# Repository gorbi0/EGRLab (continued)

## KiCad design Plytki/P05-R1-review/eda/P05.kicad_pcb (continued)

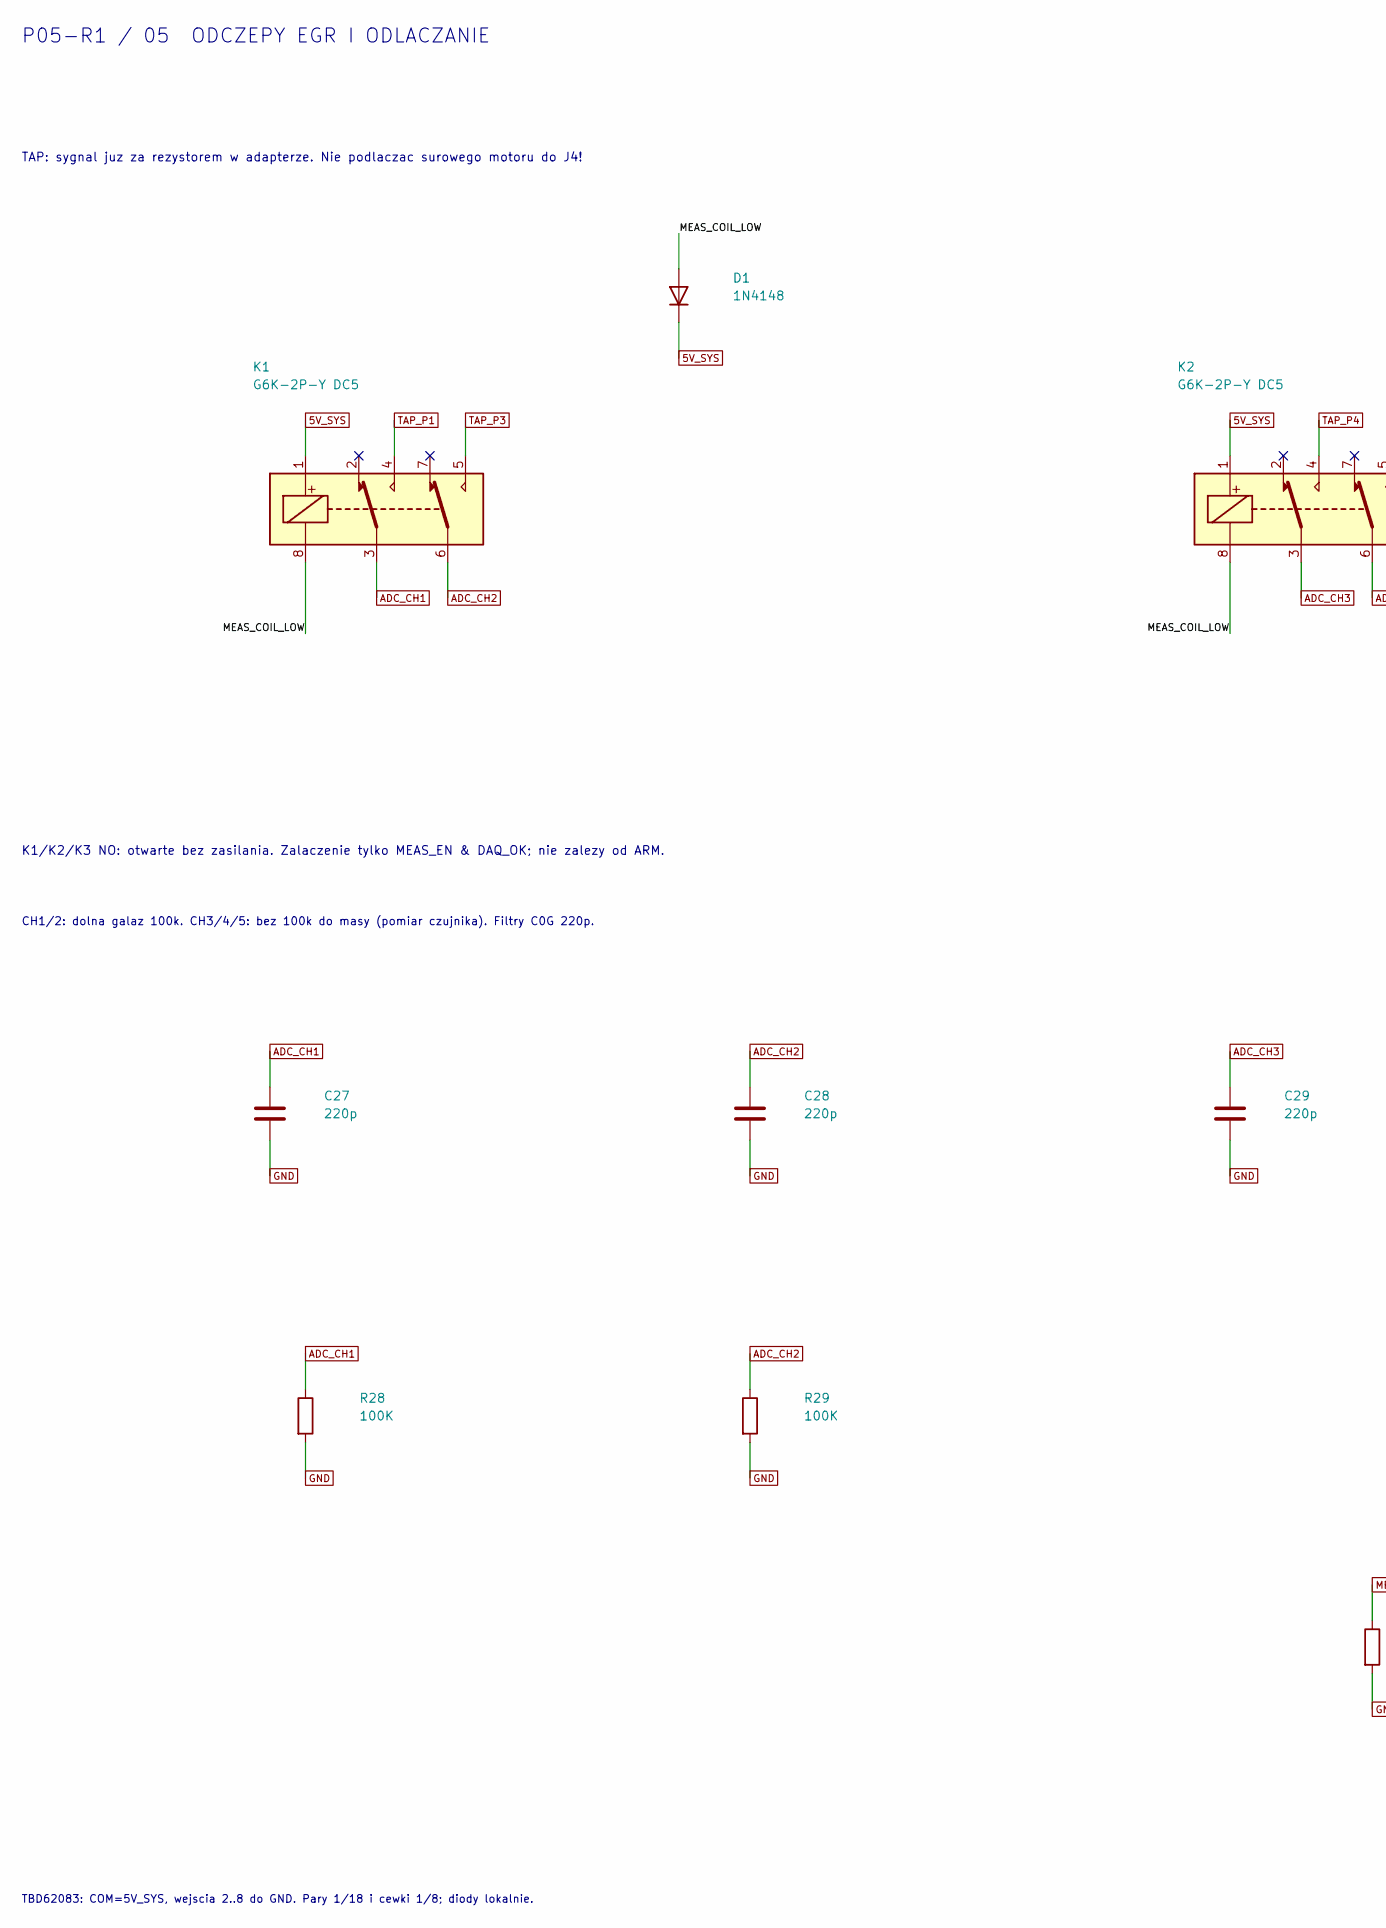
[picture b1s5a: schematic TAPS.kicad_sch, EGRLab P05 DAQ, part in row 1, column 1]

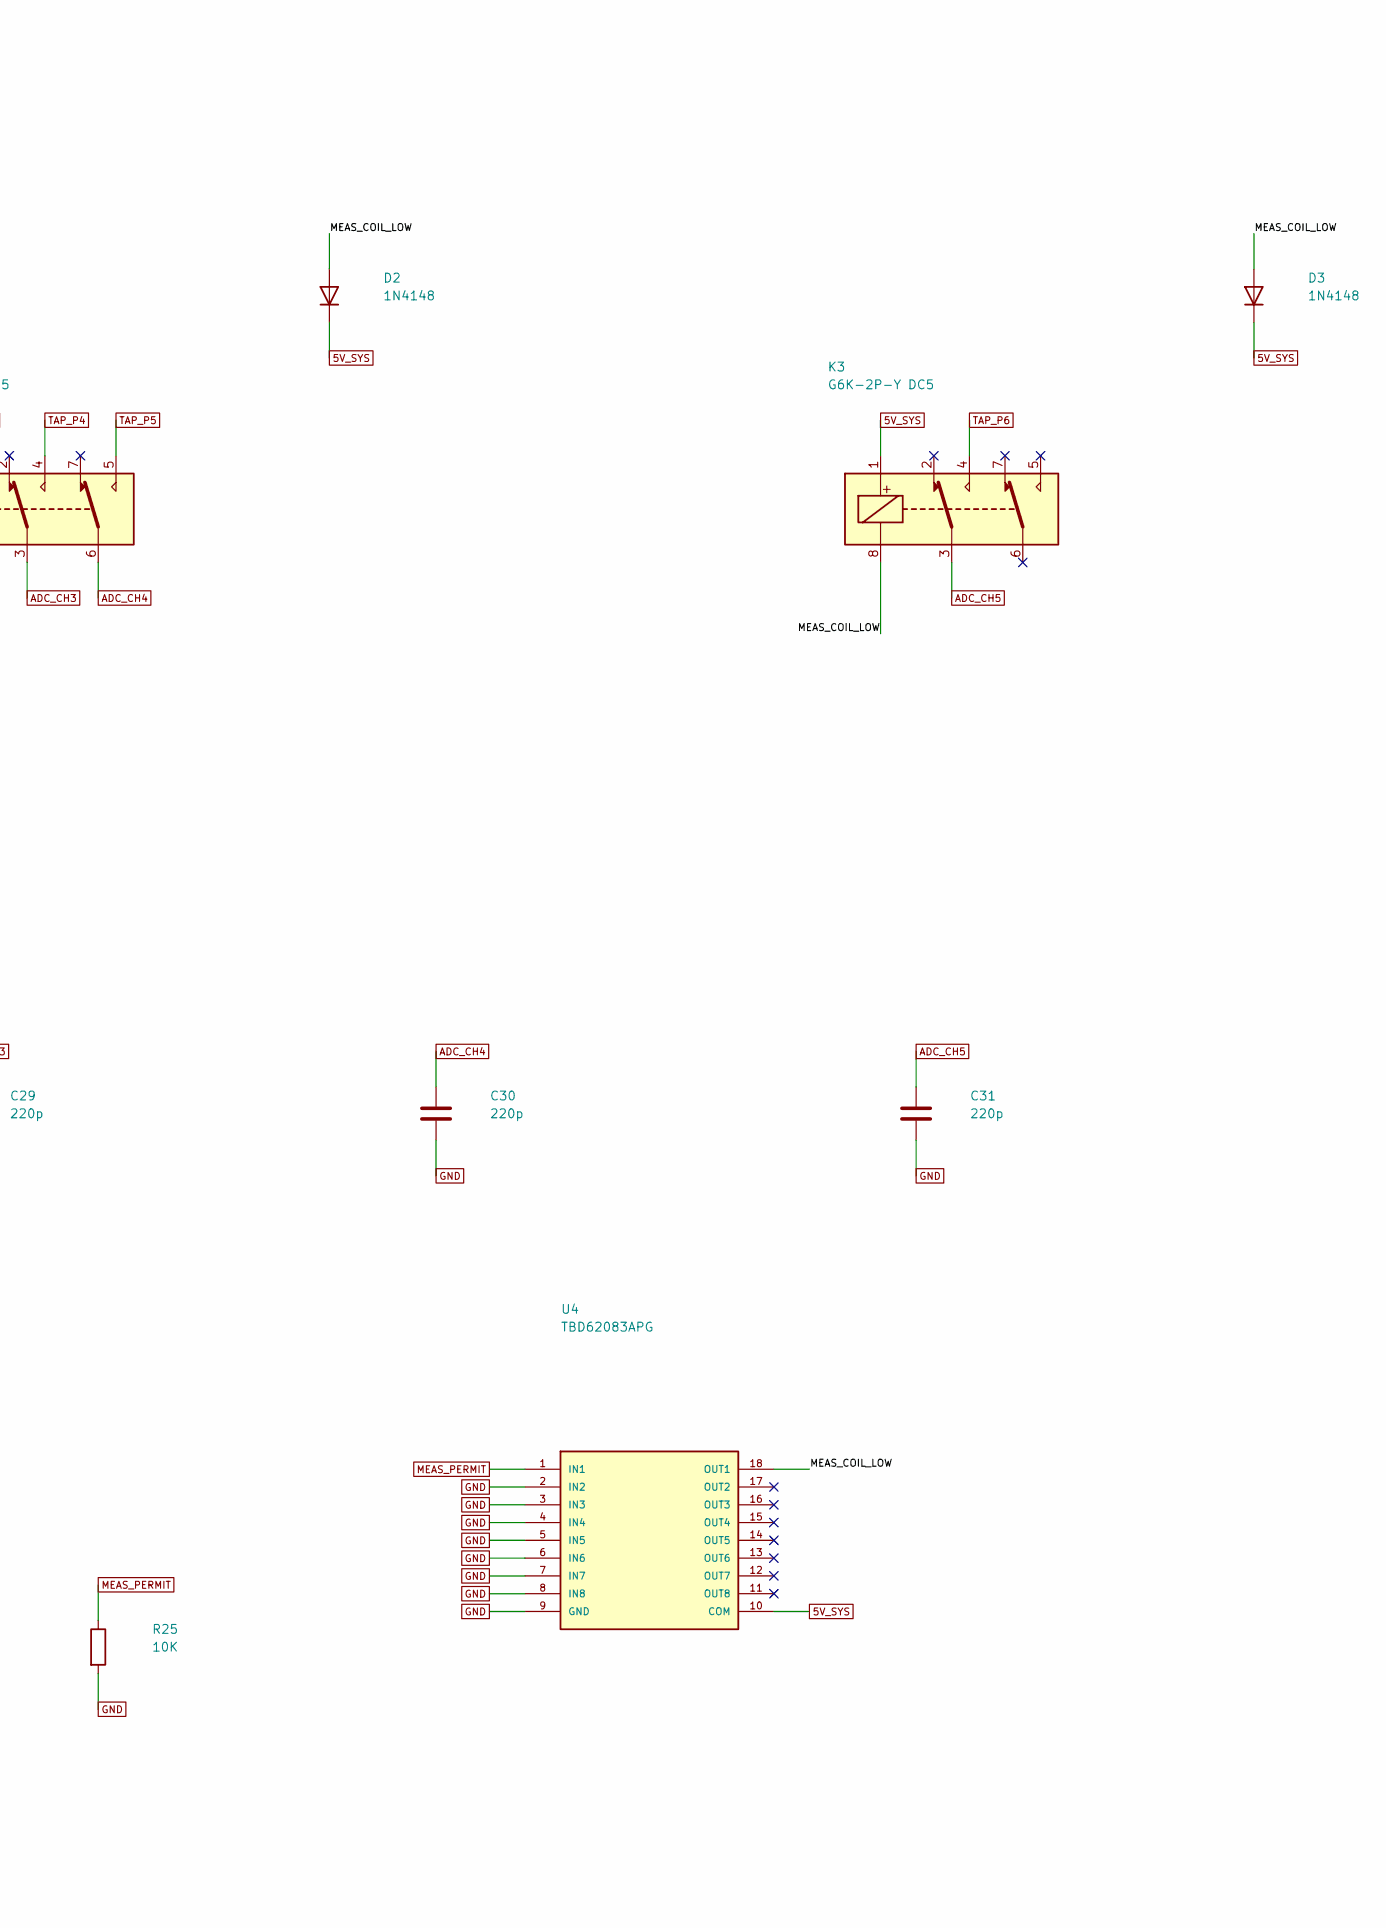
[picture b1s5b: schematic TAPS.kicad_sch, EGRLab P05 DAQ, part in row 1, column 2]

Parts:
C27, C28, C29, C30, C31: 220p; C_0805_2012Metric; MPN C0G 50V 5% 220p
D1, D2, D3: 1N4148; D_DO-35_SOD27_P7.62mm_Horizontal; MPN 1N4148
K1, K2, K3: G6K-2P-Y DC5; Relay_DPDT_Omron_G6K-2P-Y; MPN G6K-2P-Y DC5
R25: 10K; R_Axial_DIN0207_L6.3mm_D2.5mm_P10.16mm_Horizontal; MPN metal film resistor 10K 1%
R28, R29: 100K; R_Axial_DIN0207_L6.3mm_D2.5mm_P10.16mm_Horizontal; MPN MBB0207 precision metal film 100K 0.1%
U4: TBD62083APG; DIP-18_W7.62mm; MPN TBD62083APG

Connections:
5V_SYS: D1.1 (K), D2.1 (K), D3.1 (K), K1.1, K2.1, K3.1, U4.10 (COM); also elsewhere on the board
/TAPS/MEAS_COIL_LOW: D1.2 (A), D2.2 (A), D3.2 (A), K1.8, K2.8, K3.8, U4.18 (OUT1)
ADC_CH1: C27.1, K1.3, R28.1; also elsewhere on the board
ADC_CH2: C28.1, K1.6, R29.1; also elsewhere on the board
ADC_CH3: C29.1, K2.3; also elsewhere on the board
ADC_CH4: C30.1, K2.6; also elsewhere on the board
ADC_CH5: C31.1, K3.3; also elsewhere on the board
GND: C27.2, C28.2, C29.2, C30.2, C31.2, R25.2, R28.2, R29.2, U4.2 (IN2), U4.3 (IN3), U4.4 (IN4), U4.5 (IN5), U4.6 (IN6), U4.7 (IN7), U4.8 (IN8), U4.9 (GND); also elsewhere on the board
MEAS_PERMIT: R25.1, U4.1 (IN1); also elsewhere on the board
TAP_P1: K1.4; also elsewhere on the board
TAP_P3: K1.5; also elsewhere on the board
TAP_P4: K2.4; also elsewhere on the board
TAP_P5: K2.5; also elsewhere on the board
TAP_P6: K3.4; also elsewhere on the board

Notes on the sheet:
TAP: sygnal juz za rezystorem w adapterze. Nie podlaczac surowego motoru do J4!
K1/K2/K3 NO: otwarte bez zasilania. Zalaczenie tylko MEAS_EN & DAQ_OK; nie zalezy od ARM.
CH1/2: dolna galaz 100k. CH3/4/5: bez 100k do masy (pomiar czujnika). Filtry C0G 220p.
TBD62083: COM=5V_SYS, wejscia 2..8 do GND. Pary 1/18 i cewki 1/8; diody lokalnie.
P05-R1 / 05 ODCZEPY EGR I ODLACZANIE

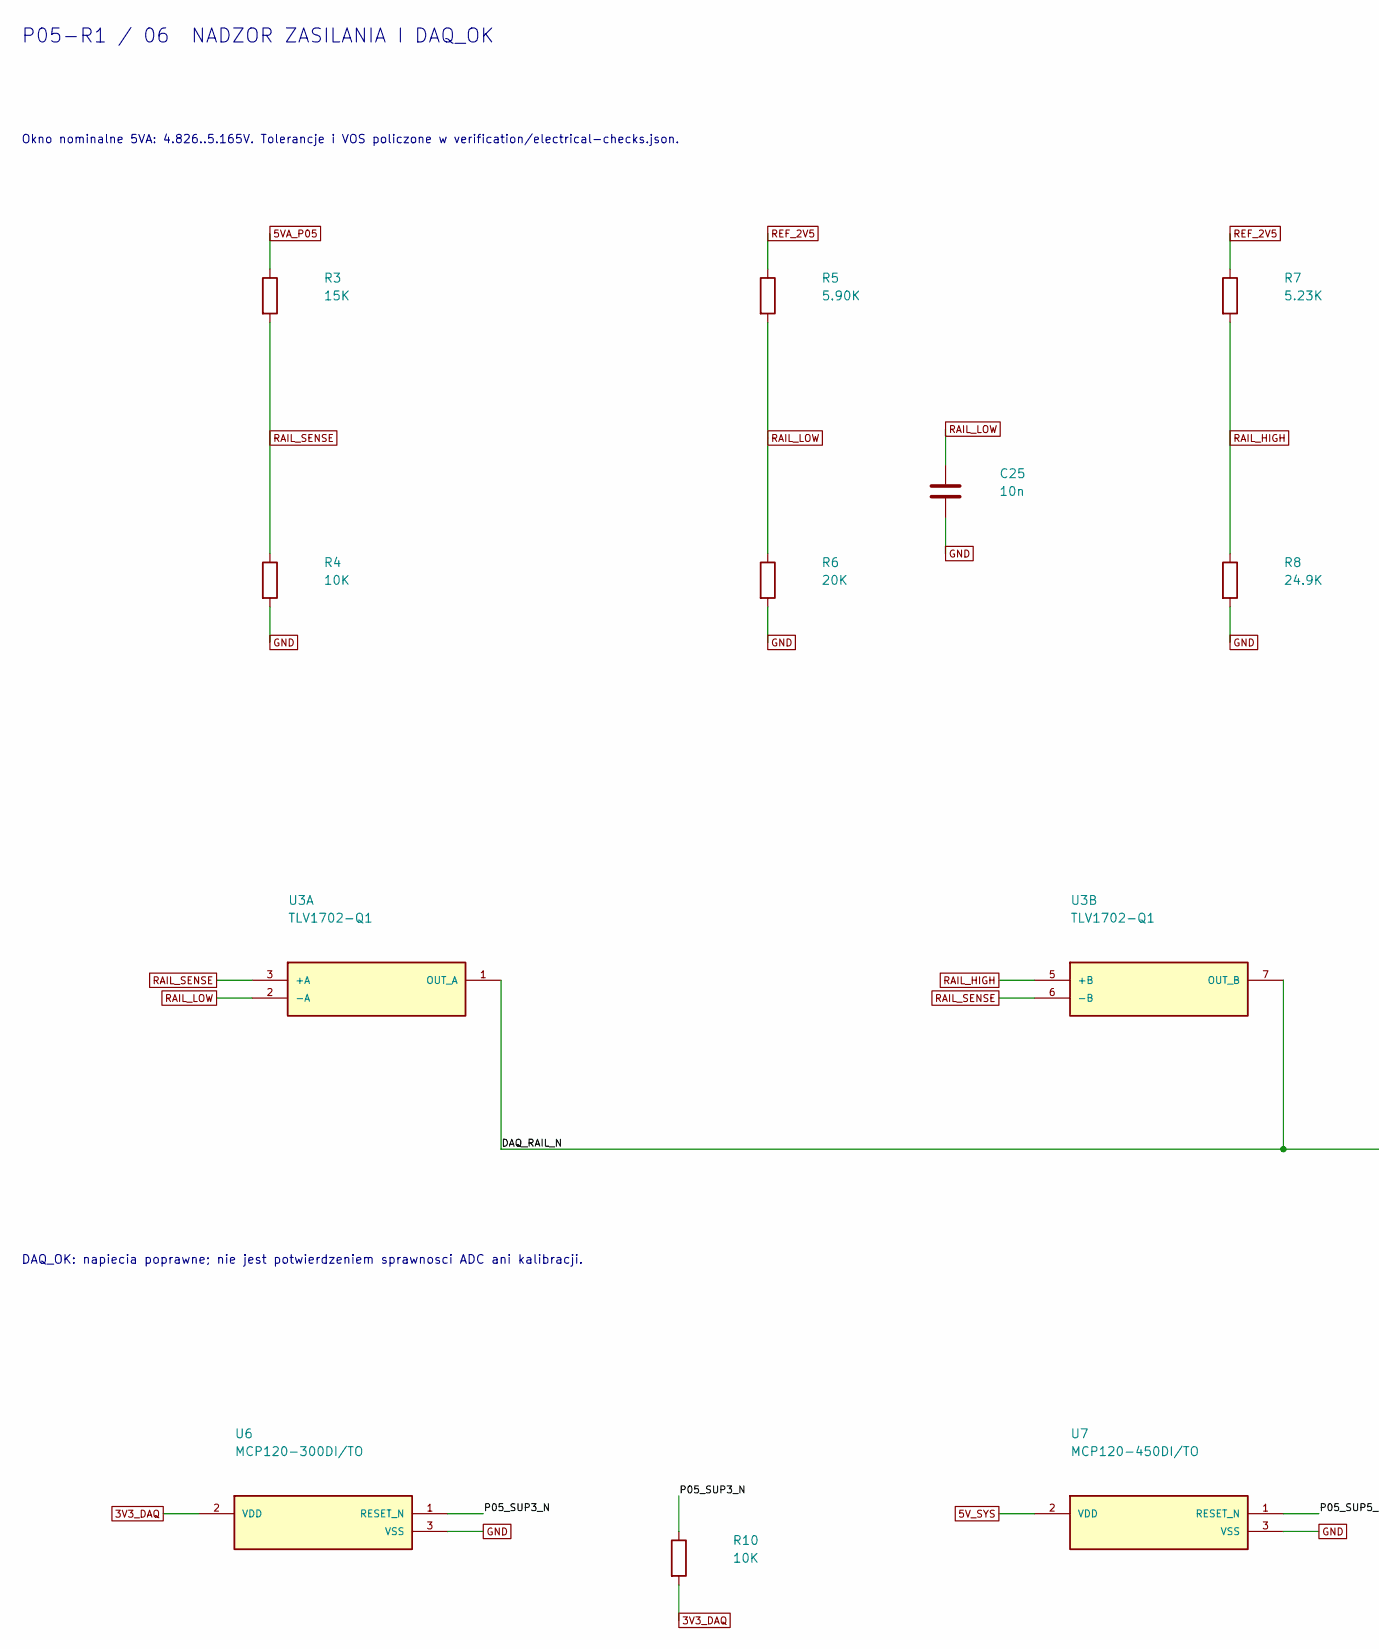
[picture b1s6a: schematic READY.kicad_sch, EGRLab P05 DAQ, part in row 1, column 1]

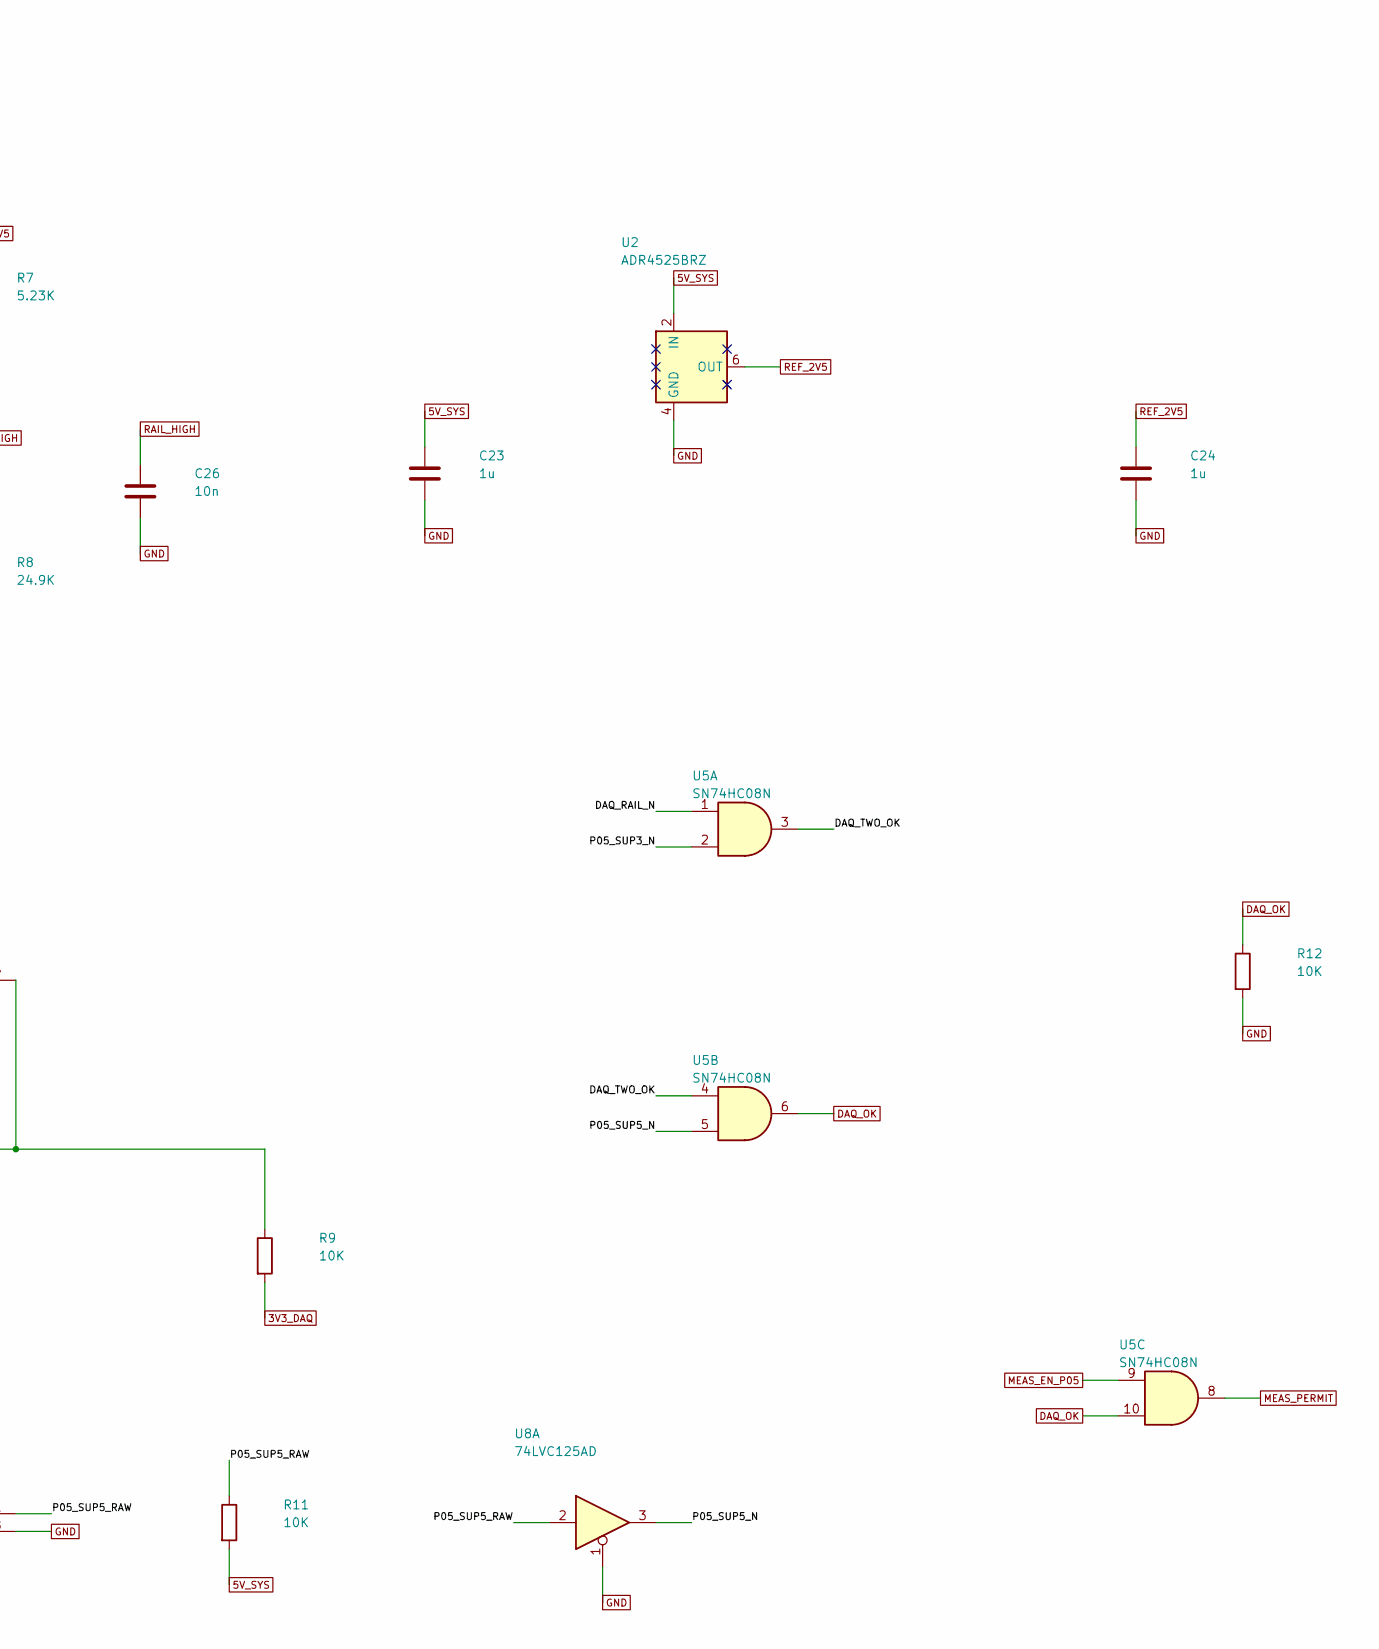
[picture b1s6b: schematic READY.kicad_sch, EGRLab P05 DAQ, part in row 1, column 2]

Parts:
C23, C24: 1u; C_0805_2012Metric; MPN X7R 25V 10% 1u
C25, C26: 10n; C_0805_2012Metric; MPN X7R 25V 10% 10n
R3: 15K; R_Axial_DIN0207_L6.3mm_D2.5mm_P10.16mm_Horizontal; MPN MBB0207 precision metal film 15K 0.1%
R4: 10K; R_Axial_DIN0207_L6.3mm_D2.5mm_P10.16mm_Horizontal; MPN MBB0207 precision metal film 10K 0.1%
R5: 5.90K; R_Axial_DIN0207_L6.3mm_D2.5mm_P10.16mm_Horizontal; MPN MBB0207 precision metal film 5.90K 0.1%
R6: 20K; R_Axial_DIN0207_L6.3mm_D2.5mm_P10.16mm_Horizontal; MPN MBB0207 precision metal film 20K 0.1%
R7: 5.23K; R_Axial_DIN0207_L6.3mm_D2.5mm_P10.16mm_Horizontal; MPN MBB0207 precision metal film 5.23K 0.1%
R8: 24.9K; R_Axial_DIN0207_L6.3mm_D2.5mm_P10.16mm_Horizontal; MPN MBB0207 precision metal film 24.9K 0.1%
R9, R10, R11, R12: 10K; R_Axial_DIN0207_L6.3mm_D2.5mm_P10.16mm_Horizontal; MPN metal film resistor 10K 1%
U2: ADR4525BRZ; SOIC-8_3.9x4.9mm_P1.27mm; MPN ADR4525BRZ
U3: TLV1702-Q1; VSSOP-8_3x3mm_P0.65mm; MPN TLV1702AQDGKRQ1
U5: SN74HC08N; DIP-14_W7.62mm; MPN SN74HC08N
U6: MCP120-300DI/TO; TO-92_Inline_Wide; MPN MCP120-300DI/TO
U7: MCP120-450DI/TO; TO-92_Inline_Wide; MPN MCP120-450DI/TO
U8: 74LVC125AD; SOIC-14_3.9x8.7mm_P1.27mm; MPN 74LVC125AD,118

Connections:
3V3_DAQ: R9.2, R10.2, U6.2 (VDD); also elsewhere on the board
5VA_P05: R3.1; also elsewhere on the board
5V_SYS: C23.1, R11.2, U2.2 (IN), U7.2 (VDD); also elsewhere on the board
/READY/DAQ_RAIL_N: R9.1, U3.1 (OUT_A), U3.7 (OUT_B), U5.1
/READY/DAQ_TWO_OK: U5.3, U5.4
/READY/P05_SUP3_N: R10.1, U5.2, U6.1 (RESET_N)
/READY/P05_SUP5_N: U5.5, U8.3
/READY/P05_SUP5_RAW: R11.1, U7.1 (RESET_N), U8.2
DAQ_OK: R12.1, U5.6, U5.10; also elsewhere on the board
GND: C23.2, C24.2, C25.2, C26.2, R4.2, R6.2, R8.2, R12.2, U2.4 (GND), U6.3 (VSS), U7.3 (VSS), U8.1; also elsewhere on the board
MEAS_EN_P05: U5.9; also elsewhere on the board
MEAS_PERMIT: U5.8; also elsewhere on the board
RAIL_HIGH: C26.1, R7.2, R8.1, U3.5 (+B); also elsewhere on the board
RAIL_LOW: C25.1, R5.2, R6.1, U3.2 (-A); also elsewhere on the board
RAIL_SENSE: R3.2, R4.1, U3.3 (+A), U3.6 (-B); also elsewhere on the board
REF_2V5: C24.1, R5.1, R7.1, U2.6 (OUT); also elsewhere on the board

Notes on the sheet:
Okno nominalne 5VA: 4.826..5.165V. Tolerancje i VOS policzone w verification/electrical-checks.json.
DAQ_OK: napiecia poprawne; nie jest potwierdzeniem sprawnosci ADC ani kalibracji.
P05-R1 / 06 NADZOR ZASILANIA I DAQ_OK

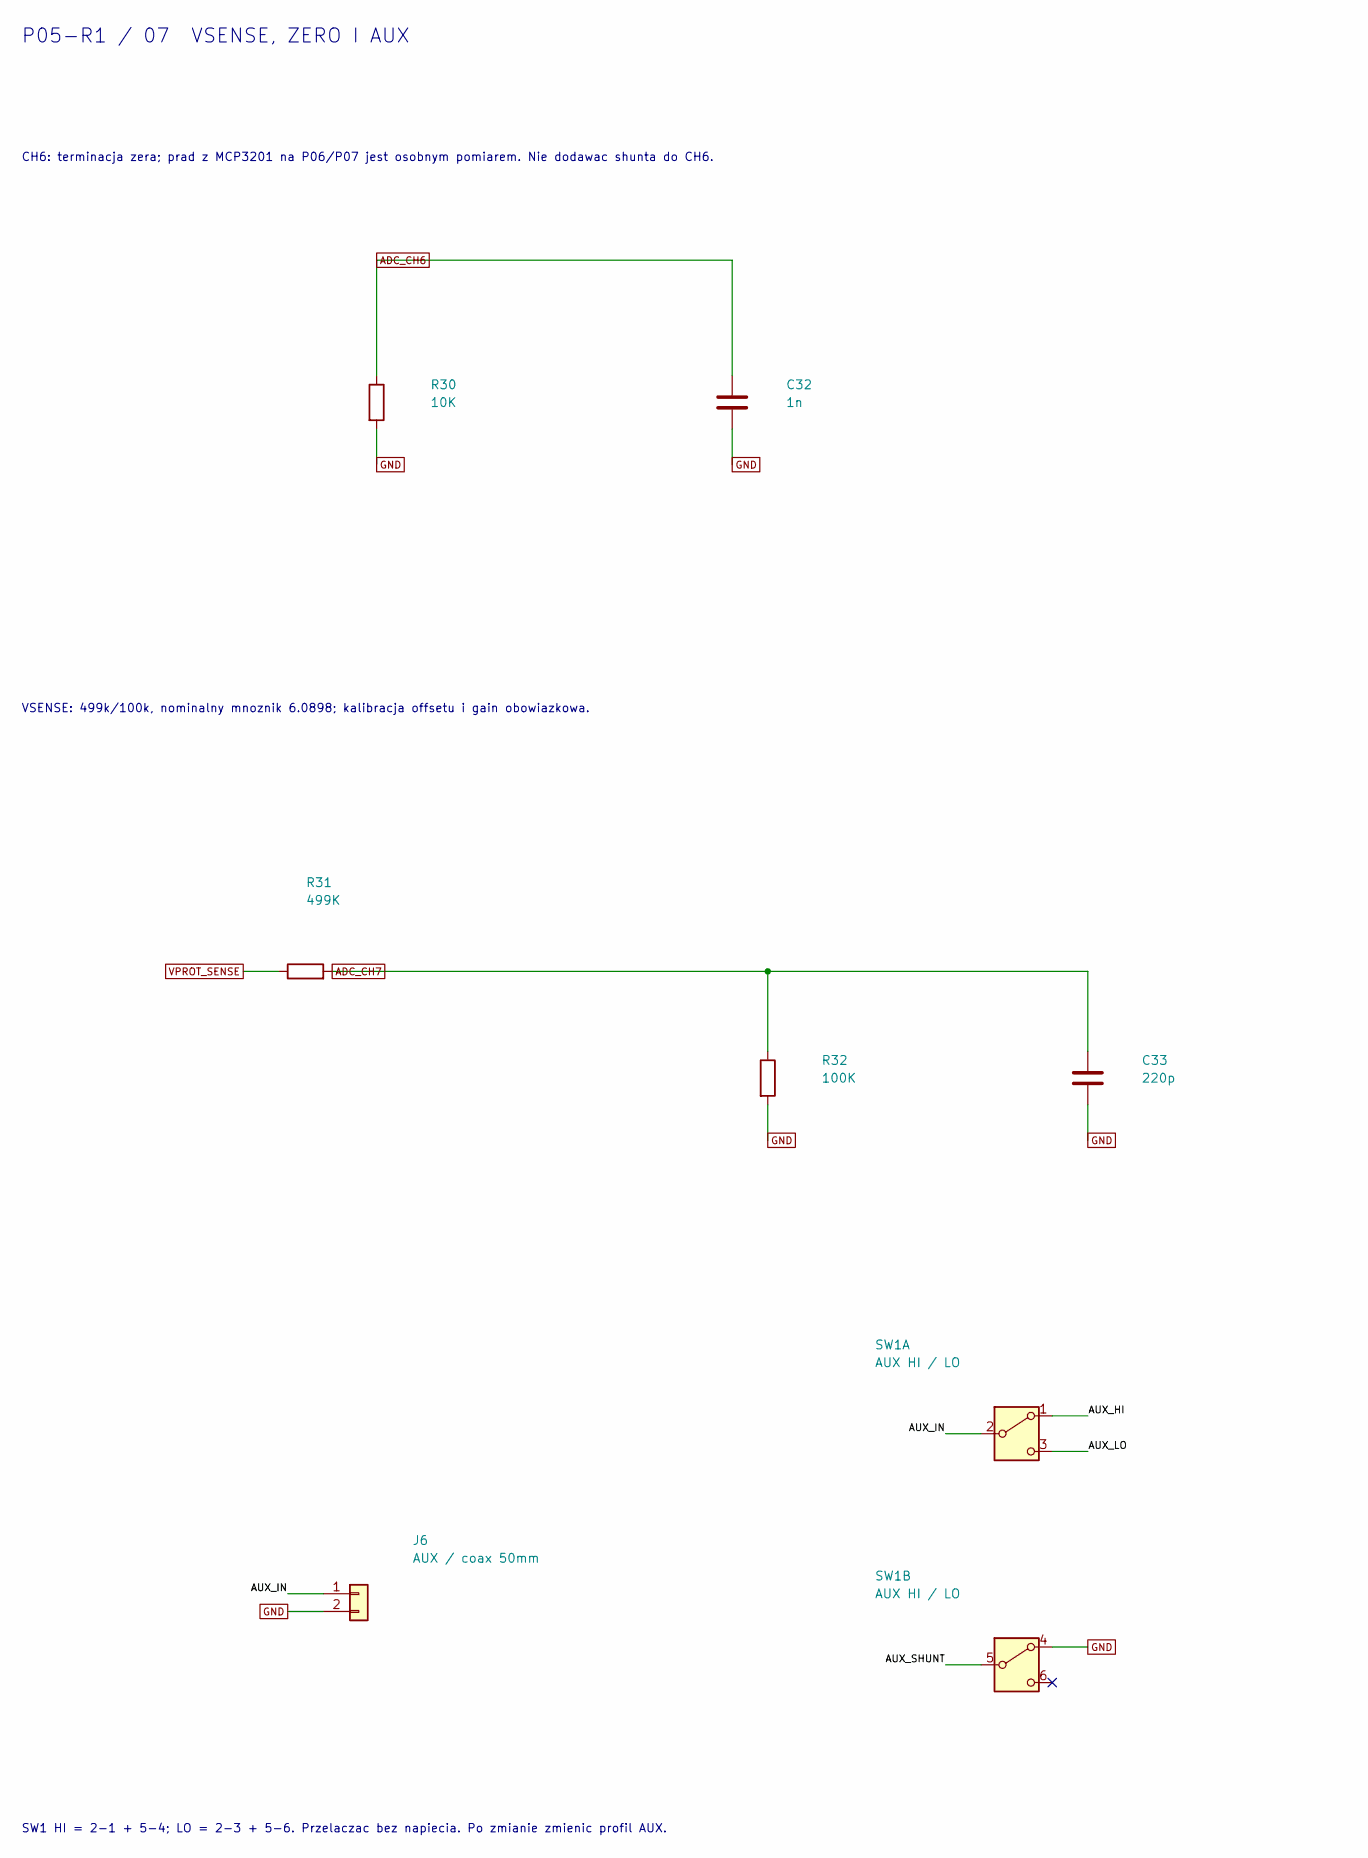
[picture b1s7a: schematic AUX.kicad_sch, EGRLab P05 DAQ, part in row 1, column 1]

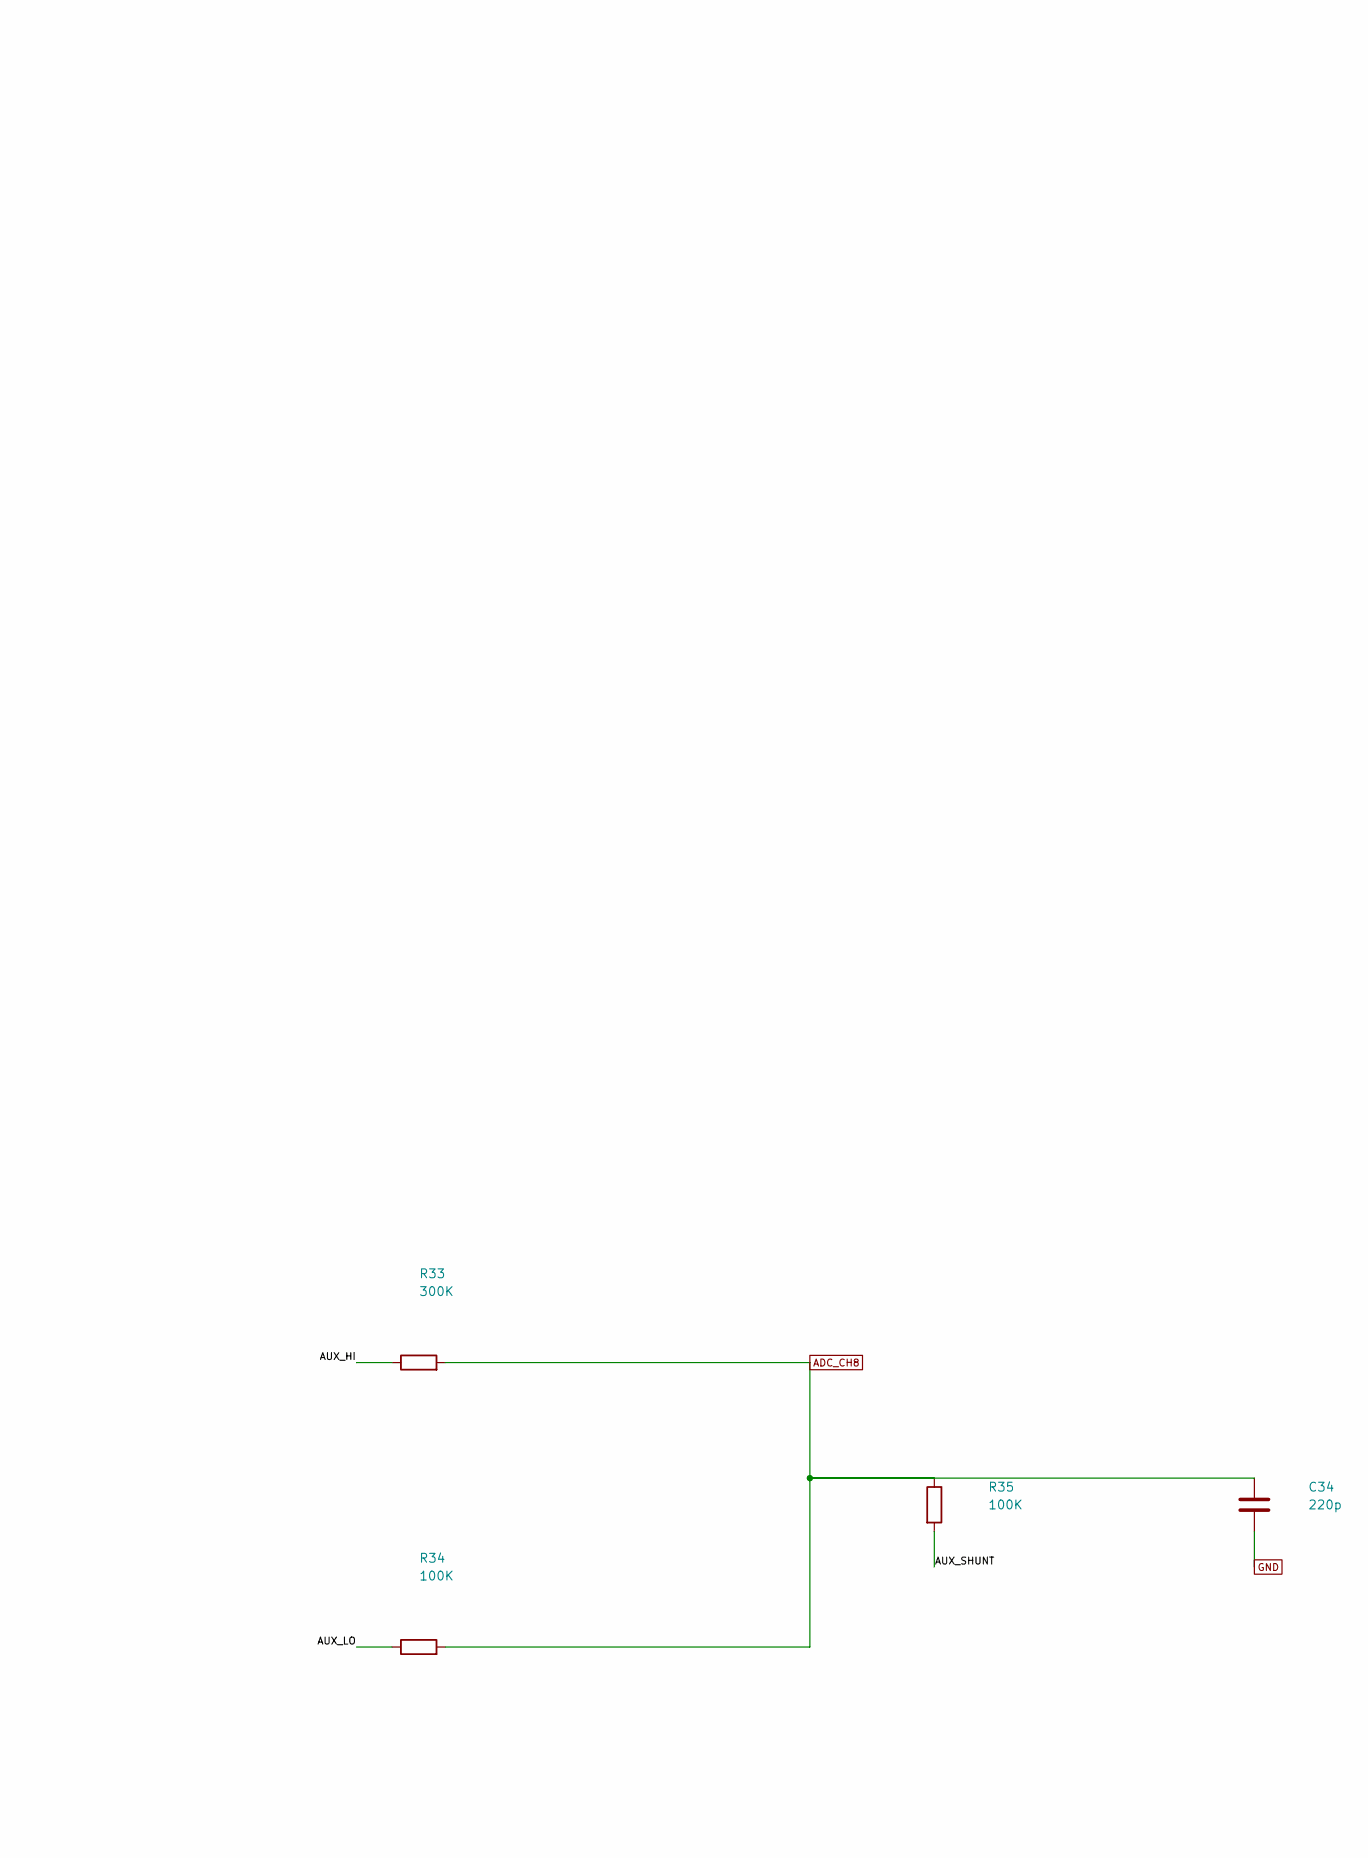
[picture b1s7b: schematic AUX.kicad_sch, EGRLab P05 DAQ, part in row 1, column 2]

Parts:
C32: 1n; C_0805_2012Metric; MPN X7R 25V 10% 1n
C33, C34: 220p; C_0805_2012Metric; MPN C0G 50V 5% 220p
J6: AUX / coax 50mm; PTH_AUX_2; MPN insulated panel BNC + RG174 50mm
R30: 10K; R_Axial_DIN0207_L6.3mm_D2.5mm_P10.16mm_Horizontal; MPN metal film resistor 10K 1%
R31: 499K; R_Axial_DIN0207_L6.3mm_D2.5mm_P10.16mm_Horizontal; MPN MBB0207 precision metal film 499K 0.1%
R32, R34, R35: 100K; R_Axial_DIN0207_L6.3mm_D2.5mm_P10.16mm_Horizontal; MPN MBB0207 precision metal film 100K 0.1%
R33: 300K; R_Axial_DIN0207_L6.3mm_D2.5mm_P10.16mm_Horizontal; MPN MBB0207 precision metal film 300K 0.1%
SW1: AUX HI / LO; CK_7201SYCBE; MPN 7201SYCBE

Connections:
/AUX/AUX_HI: R33.1, SW1.1 (A)
/AUX/AUX_IN: J6.1, SW1.2 (B)
/AUX/AUX_LO: R34.1, SW1.3 (C)
/AUX/AUX_SHUNT: R35.2, SW1.5 (B)
ADC_CH6: C32.1, R30.1; also elsewhere on the board
ADC_CH7: C33.1, R31.2, R32.1; also elsewhere on the board
ADC_CH8: C34.1, R33.2, R34.2, R35.1; also elsewhere on the board
GND: C32.2, C33.2, C34.2, J6.2, R30.2, R32.2, SW1.4 (A); also elsewhere on the board
VPROT_SENSE: R31.1; also elsewhere on the board

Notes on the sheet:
CH6: terminacja zera; prad z MCP3201 na P06/P07 jest osobnym pomiarem. Nie dodawac shunta do CH6.
VSENSE: 499k/100k, nominalny mnoznik 6.0898; kalibracja offsetu i gain obowiazkowa.
SW1 HI = 2-1 + 5-4; LO = 2-3 + 5-6. Przelaczac bez napiecia. Po zmianie zmienic profil AUX.
P05-R1 / 07 VSENSE, ZERO I AUX
